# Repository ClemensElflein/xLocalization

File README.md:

# xLocalization [inactive]

The xLocalization project aims to provide a simple to use, low cost indoor positioning system for hobbyist use.

# Current State
The PCB works fine. Initial testing with the official decawave firmware showed that the localization works, but is not even close to precise enough for my intended application.
Therefore, this project currently will no longer be worked on. There is currently no code for the ESP8266 available.

# License
<br />This work is licensed under a <a rel="license" href="http://creativecommons.org/licenses/by-nc-sa/4.0/">Creative Commons Attribution-NonCommercial-ShareAlike 4.0 International License</a>.

Feel free to use the design in your projects, but don't try to sell the design or products based on it without getting my consent first.

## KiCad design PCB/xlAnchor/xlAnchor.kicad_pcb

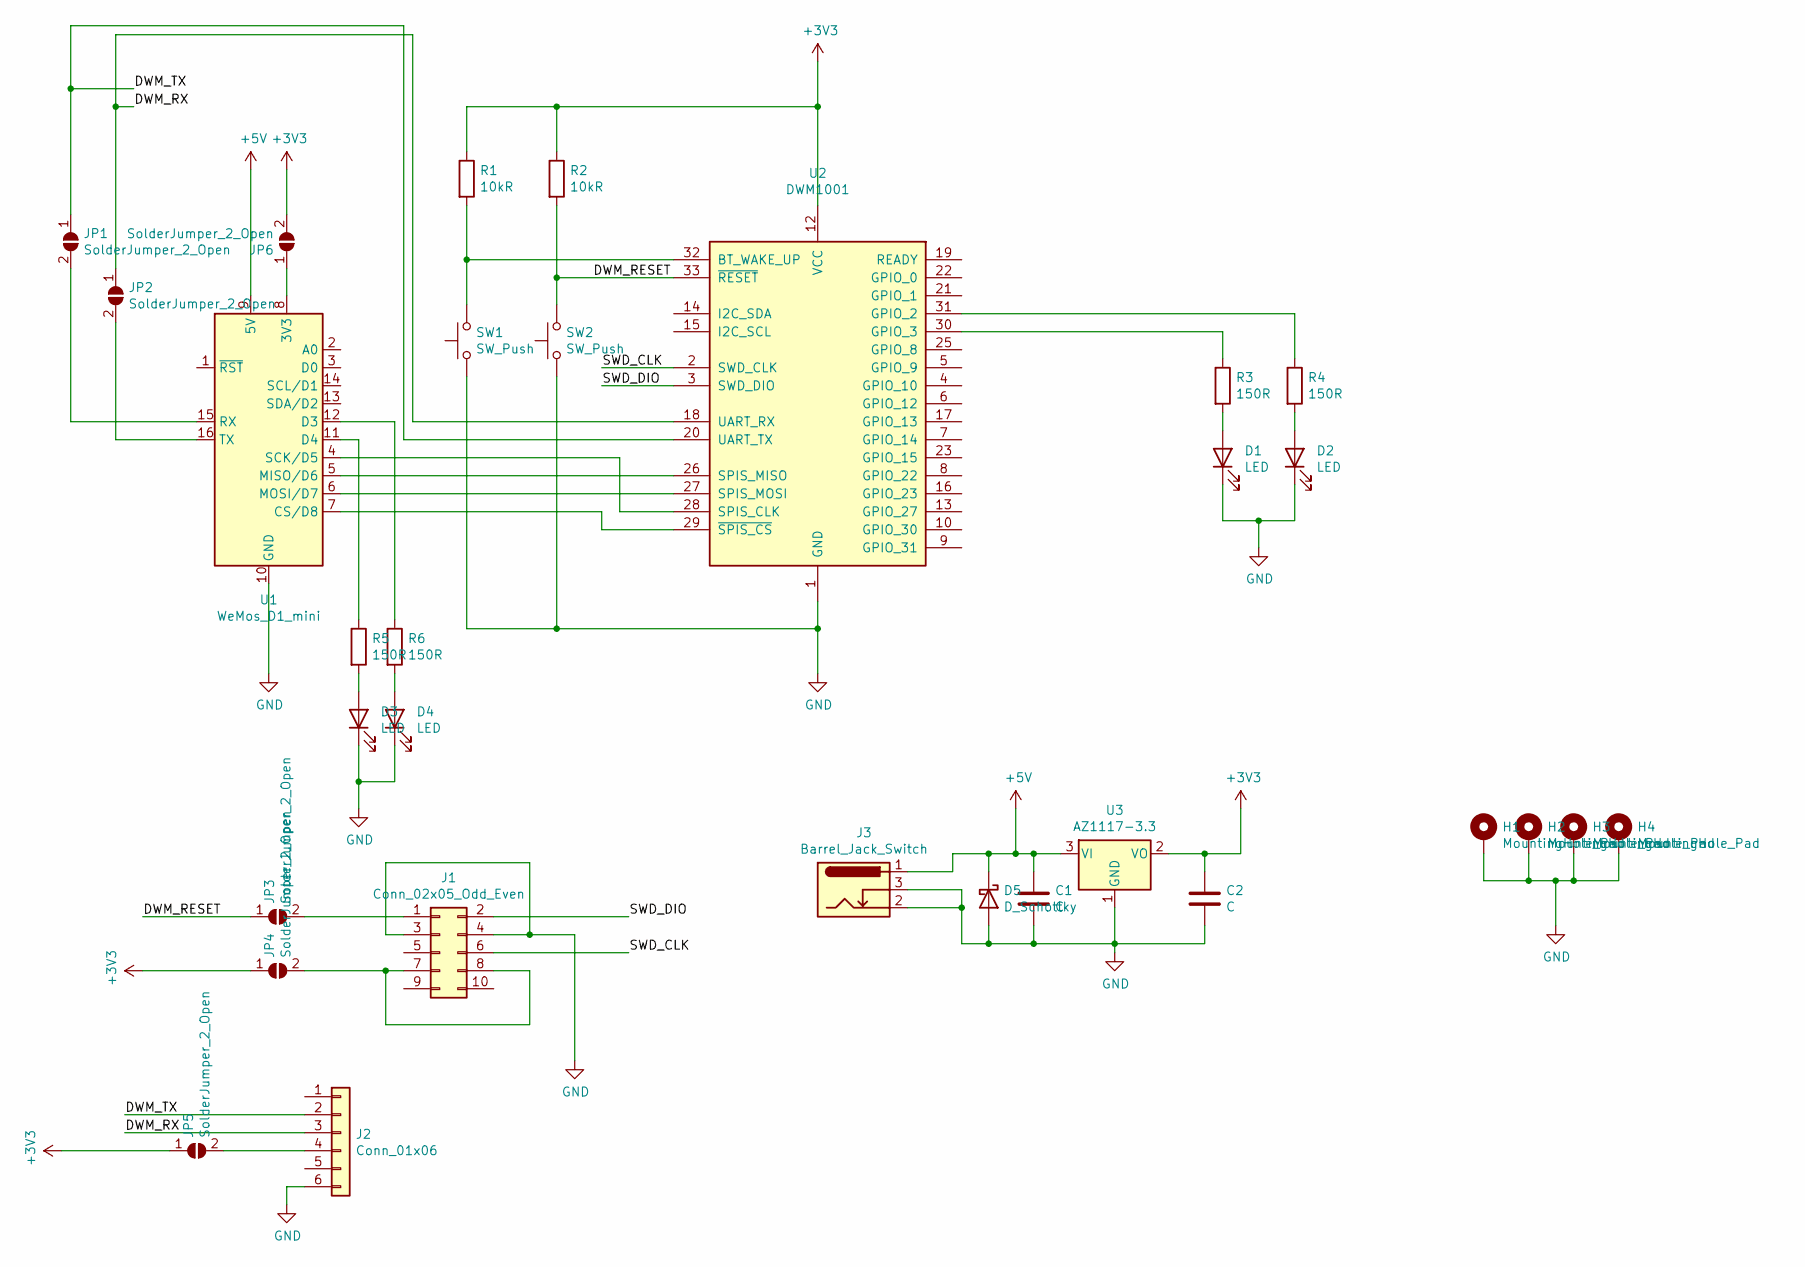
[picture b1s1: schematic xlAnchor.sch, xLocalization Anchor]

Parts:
C1, C2: C; C_0805_2012Metric
D1, D2, D3, D4: LED; LED_0805_2012Metric_Pad1.15x1.40mm_HandSolder
D5: D_Schottky; D_SOD-123
H1, H2, H3, H4: MountingHole_Pad; MountingHole_3.2mm_M3_DIN965_Pad
J1: Conn_02x05_Odd_Even; PinSocket_2x05_P2.54mm_Vertical
J2: Conn_01x06; PinHeader_1x06_P2.54mm_Vertical
J3: Barrel_Jack_Switch; BarrelJack_Horizontal
JP1, JP2, JP3, JP4, JP5, JP6: SolderJumper_2_Open; SolderJumper-2_P1.3mm_Open_Pad1.0x1.5mm
R1, R2: 10kR; R_0805_2012Metric_Pad1.20x1.40mm_HandSolder
R3, R4, R5, R6: 150R; R_0805_2012Metric_Pad1.20x1.40mm_HandSolder
SW1, SW2: SW_Push; SW_PUSH_6mm
U1: WeMos_D1_mini; WEMOS_D1_mini_light
U2: DWM1001; DecaWave_DWM1001
U3: AZ1117-3.3; SOT-223-3_TabPin2

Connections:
+3V3: C2.1, JP4.1 (A), JP5.1 (A), JP6.2 (B), R1.1, R2.1, U2.12 (VCC), U3.2 (VO)
+5V: C1.1, D5.1 (K), J3.1, U1.9 (5V), U3.3 (VI)
/DWM_RESET: JP3.1 (A), R2.2, SW2.2, U2.33 (~RESET)
/DWM_RX: J2.3, JP2.1 (A), U2.18 (UART_RX)
/DWM_TX: J2.2, JP1.1 (A), U2.20 (UART_TX)
/SWD_CLK: J1.6, U2.2 (SWD_CLK)
/SWD_DIO: J1.2, U2.3 (SWD_DIO)
GND: C1.2, C2.2, D1.1 (K), D2.1 (K), D3.1 (K), D4.1 (K), D5.2 (A), H1.1, H2.1, H3.1, H4.1, J1.3, J1.4, J2.6, J3.2, J3.3, SW1.1, SW2.1, U1.10 (GND), U2.1 (GND), U2.11 (GND), U2.24 (GND), U2.34 (GND), U3.1 (GND)
unnamed: D1.2 (A), R3.2
unnamed: D2.2 (A), R4.2
unnamed: D3.2 (A), R5.2
unnamed: D4.2 (A), R6.2
unnamed: J1.1, JP3.2 (B)
unnamed: J1.7, J1.8, JP4.2 (B)
unnamed: J2.4, JP5.2 (B)
unnamed: JP1.2 (B), U1.15 (RX)
unnamed: JP2.2 (B), U1.16 (TX)
unnamed: JP6.1 (A), U1.8 (3V3)
unnamed: R1.2, SW1.2, U2.32 (BT_WAKE_UP)
unnamed: R3.1, U2.30 (GPIO_3)
unnamed: R4.1, U2.31 (GPIO_2)
unnamed: R5.1, U1.11 (D4)
unnamed: R6.1, U1.12 (D3)
unnamed: U1.4 (SCK/D5), U2.28 (SPIS_CLK)
unnamed: U1.5 (MISO/D6), U2.26 (SPIS_MISO)
unnamed: U1.6 (MOSI/D7), U2.27 (SPIS_MOSI)
unnamed: U1.7 (CS/D8), U2.29 (~SPIS_CS)

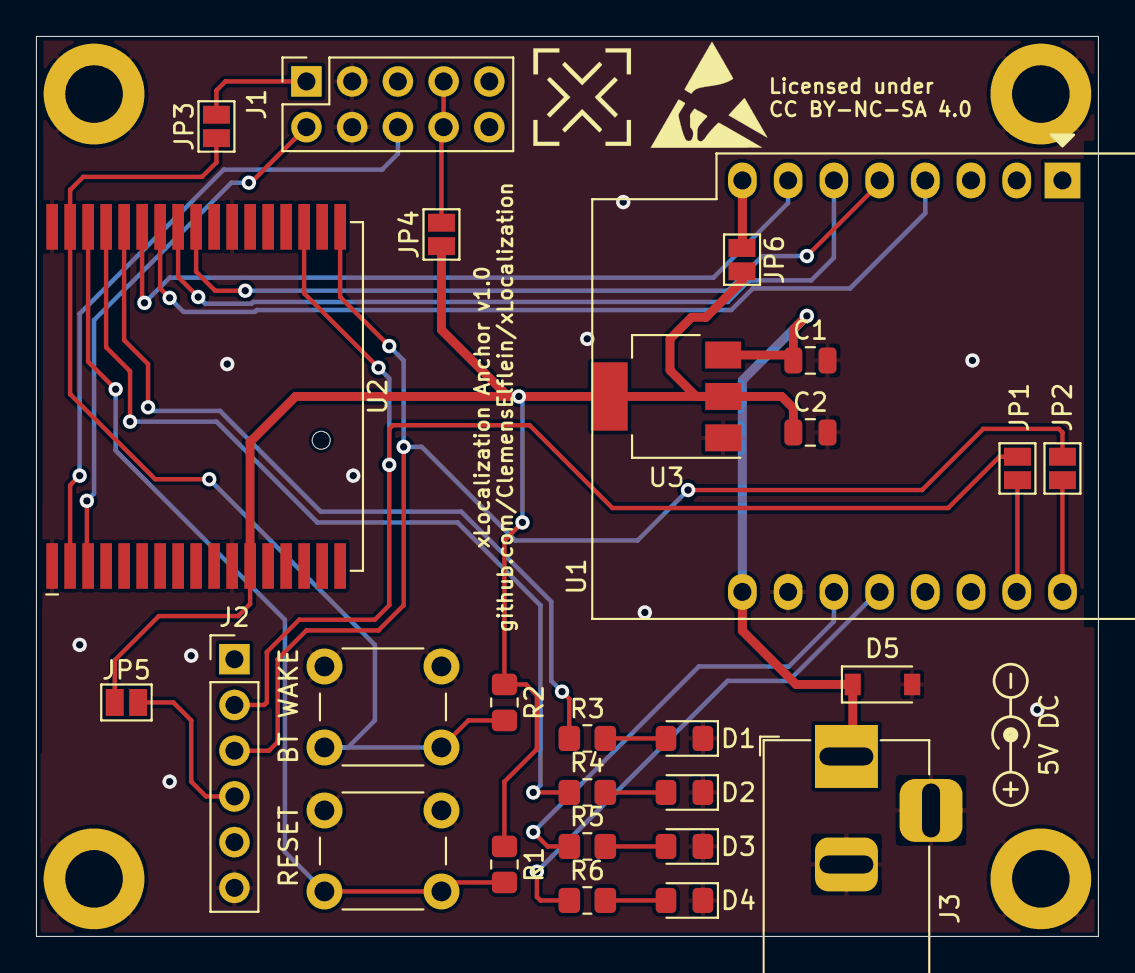
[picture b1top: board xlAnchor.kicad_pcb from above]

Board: 2 copper layers, 59.0 x 50.0 mm, 31 parts (0 on the bottom side), 27 nets.

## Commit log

2021-11-05 added license
2021-11-05 added anchor schematic and pcb
2021-11-06 ordered first batch of PCBs

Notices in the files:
PCB/xlAnchor/xlAnchor.kicad_pcb:
CC BY-NC-SA 4.0
README.md:
License: CC BY-NC-SA 4.0
